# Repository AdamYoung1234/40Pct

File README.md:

The SmallFry 40% Board
=====

##NOTICE
* This repo is a fork of Regack's 40Pct
* This repo is under CC-BY-SA 3.0 Liscense
* PLEASE MAKE SURE YOU FULLY UNDERSTAND THIS LISCENSE BEFORE YOU USE THE DESIGN.
* 请确保在使用之前完全理解了 CC-BY-SA 3.0协议.

## To-do list
* Add the global backlight

## v0.11
* Change the cystal package to HC49
* Change the mini USB package from SMD to TH

## v0.8-v0.10
* I forget everything that I did, lots of little things
* fixed some unconnected pads (oops)
* cleaned up silkscreens again
* fixed diode pads to fit SOD-123 footprint
* fixed BOM info for components
* rounded PCB edges
* replaced slotted holes with... holes
* added Vcc and Gnd pins to LED expansion
* changed LED expansion pins to 2.54 pitch

## v0.7 - 2013.10.20
* cleaned up silkscreens
* moved 'ROW5' expansion to GPIO7 (still ATMEGA32U4 pin8/PB0)
* added notes
* cleaned up and removed extra libs/mods

## v0.6 - 2013.10.16
* pulled extra pin for ROW5 from ATMEGA pin 8/PB0
* changed drills for holes/slots to work with OSHpark 
* added GPIO4, GPIO5, GPIO6 connectors to ATMEGA pins 26/PD6, 22/PD5, 11/PB3
* ran row and GPIO to 1.27mm headers on right-side of board for interconnect (ribbon cable spacing)

## v0.5 - 2013.09.20
* added back missing slot on right side of board
* added LEDs for optional keys from v0.4
* generated pcb image * not sure why slots don't render properly
* removed bottom-of-board expansion pins

## v0.4 - 2013.09.19
* added optional 1.25+1.0 and 1.0+1.25 for right-shift/fn keys

## v0.3 - 2013.09.18
* based on the GH60 Rev B PCB
* SMT ATMEGA32U4 and other components on back of board
* Expansion ports on bottom and top row
* LEDs on ESC, 'CAPS', and WASD Cluster
* Other LEDs in matrix with expansion points on top row

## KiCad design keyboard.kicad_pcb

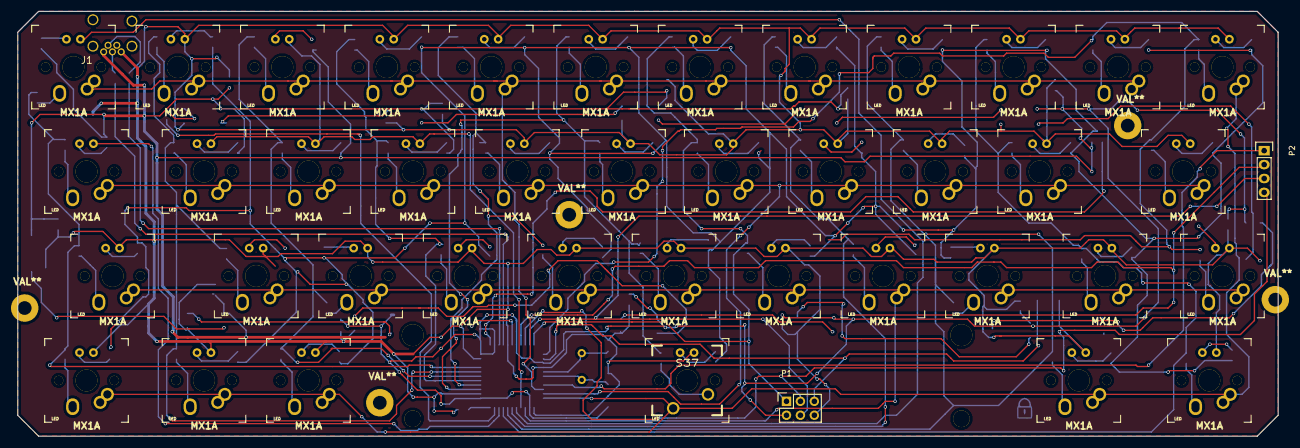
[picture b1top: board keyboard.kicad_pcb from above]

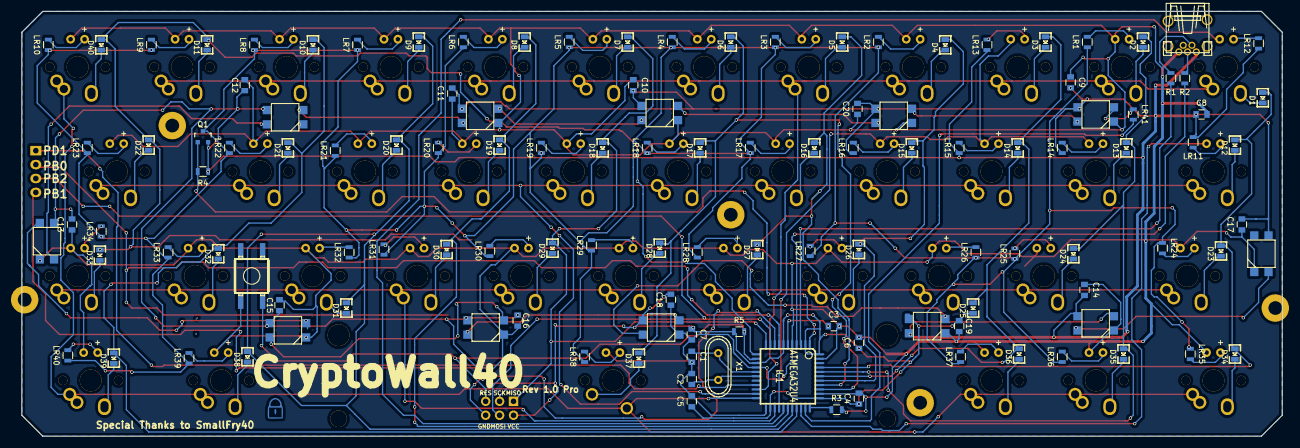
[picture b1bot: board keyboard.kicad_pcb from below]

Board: 2 copper layers, 229.9 x 77.5 mm, 210 parts (123 on the bottom side), 128 nets.

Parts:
C1, C2: 22pF; C_0805
C3, C8: 1uF; C_0805
C4, C5, C6, C7, C9, C10, C11, C12, C13, C14, C15, C16, C17, C18, C19, C20: 100nF; C_0805
D1, D2, D3, D4, D5, D6, D7, D8, D9, D10, D11, D12, D13, D14, D15, D16, D17, D18, D19, D20, D21, D22, D23, D24, D25, D26, D27, D28, D29, D30, D31, D32, D33, D34, D35, D36, D37, D38, D39, D40: DIODE; SM0805D
IC1: ATMEGA32U4; TQFP44
J1: USBMINI_B05; DX_USB
LED1, LED2, LED3, LED4, LED5, LED6, LED7, LED8, LED9, LED10, LED11, LED12, LED13, LED14, LED15, LED16, LED17, LED18, LED19, LED20, LED21, LED22, LED23, LED24, LED25, LED26, LED27, LED28, LED29, LED30, LED31, LED32, LED33, LED34, LED35, LED36, LED37, LED38, LED39, LED40: LED; MX1A-led
LR1, LR2, LR3, LR4, LR5, LR6, LR7, LR8, LR9, LR10, LR11, LR12, LR13, LR14, LR15, LR16, LR17, LR18, LR19, LR20, LR21, LR22, LR23, LR24, LR25, LR26, LR27, LR28, LR29, LR30, LR31, LR32, LR33, LR34, LR35, LR36, LR37, LR38, LR39, LR40, LR41: 330R; R_0805
MXLED: VAL**; PKRHC
MXLED#2, MXLED#3, MXLED#4, MXLED#5: VAL**; PKRHC
P1: ISP; Socket_Strip_Straight_2x03
P2: GPIO Port; Socket_Strip_Straight_1x04
Q1: MOS_P; SOT-23
R1, R2: 22R; R_0805
R3, R4, R5: 10K; R_0805
RGBLED1, RGBLED2, RGBLED3, RGBLED4, RGBLED5, RGBLED6, RGBLED7, RGBLED8, RGBLED9, RGBLED10, RGBLED11, RGBLED12: WS2812B
S0: DTSM-6
S1, S2, S3, S4, S5, S6, S7, S8, S9, S10, S11, S12, S13, S14, S15, S16, S17, S18, S19, S20, S21, S22, S23, S24, S25, S26, S27, S28, S29, S30, S31, S32, S33, S34, S35, S36, S38, S39, S40: MX1A; MX1ALPS
S37: MX1A; CHERRY_PCB_625H_Rev
X1: CRYSTAL; Crystal_HC49-U_Vertical

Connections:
/GPIO0: IC1.10, P1.4, P2.3
/GPIO1: IC1.9, P1.3, P2.4
/GPIO2: IC1.8, P2.2
/GPIO3: IC1.19, P2.1
/Matrix/Col0: D1.1, D12.1, D23.1, D34.1, IC1.41
/Matrix/Col1: D2.1, D13.1, D24.1, D35.1, IC1.40
/Matrix/Col2: D3.1, D14.1, D25.1, D36.1, IC1.39
/Matrix/Col3: D4.1, D15.1, D26.1, IC1.38
/Matrix/Col4: D5.1, D16.1, D27.1, IC1.37
/Matrix/Col5: D6.1, D17.1, D28.1, D37.1, IC1.36
/Matrix/Col6: D7.1, D18.1, D29.1, IC1.11, P1.1
/Matrix/Col7: D8.1, D19.1, D30.1, IC1.28
/Matrix/Col8: D9.1, D20.1, D31.1, D38.1, IC1.29
/Matrix/Col9: D10.1, D21.1, D32.1, D39.1, IC1.30
/Matrix/Col10: D11.1, D22.1, D33.1, D40.1, IC1.12
/Matrix/Row0: IC1.20, S1.1, S2.1, S3.1, S4.1, S5.1, S6.1, S7.1, S8.1, S9.1, S10.1, S11.1
/Matrix/Row1: IC1.21, S12.1, S13.1, S14.1, S15.1, S16.1, S17.1, S18.1, S19.1, S20.1, S21.1, S22.1
/Matrix/Row2: IC1.25, S23.1, S24.1, S25.1, S26.1, S27.1, S28.1, S29.1, S30.1, S31.1, S32.1, S33.1
/Matrix/Row3: IC1.22, S34.1, S35.1, S36.1, S37.1, S38.1, S39.1, S40.1
/led/Backlight: IC1.1, Q1.G, R4.2
/led/Bottom: IC1.32, LR41.2
/led/CapsLock: IC1.31, LED11.2
/led/ESC: IC1.27, LED12.2
/led/LRow0: LR1.1, LR2.1, LR3.1, LR4.1, LR5.1, LR6.1, LR7.1, LR8.1, LR9.1, LR10.1, LR17.1, LR18.1, LR19.1, LR20.1, LR21.1, LR22.1, LR23.1, LR24.1, LR25.1, LR26.1, LR27.1, LR28.1, LR29.1, LR30.1, LR31.1, LR32.1, LR33.1, LR34.1, LR35.1, LR36.1, LR37.1, LR38.1, LR39.1, LR40.1, Q1.D
/led/WASD: IC1.26, LED13.2, LED14.2, LED15.2, LED16.2
/~Res: IC1.13, P1.5, R5.2, S0.3
GND: C1.2, C2.2, C3.2, C4.2, C5.2, C6.2, C7.2, C8.2, C9.1, C10.1, C11.1, C12.1, C13.1, C14.1, C15.1, C16.1, C17.1, C18.1, C19.1, C20.1, IC1.5, IC1.15, IC1.23, IC1.35, IC1.43, J1.5, LED1.2, LED2.2, LED3.2, LED4.2, LED5.2, LED6.2, LED7.2, LED8.2, LED9.2, LED10.2, LED17.2, LED18.2, LED19.2, LED20.2, LED21.2, LED22.2, LED23.2, LED24.2, LED25.2, LED26.2, LED27.2, LED28.2, LED29.2, LED30.2, LED31.2, LED32.2, LED33.2, LED34.2, LED35.2, LED36.2, LED37.2, LED38.2, LED39.2, LED40.2, P1.6, R3.2, RGBLED1.3, RGBLED2.3, RGBLED3.3, RGBLED4.3, RGBLED5.3, RGBLED6.3, RGBLED7.3, RGBLED8.3, RGBLED9.3, RGBLED10.3, RGBLED11.3, RGBLED12.3, S0.1
unnamed: C1.1, IC1.16, X1.1
unnamed: C2.1, IC1.17, X1.2
unnamed: C3.1, IC1.6
unnamed: D1.2, S1.2
unnamed: D2.2, S2.2
unnamed: D3.2, S3.2
unnamed: D4.2, S4.2
unnamed: D5.2, S5.2
unnamed: D6.2, S6.2
unnamed: D7.2, S7.2
unnamed: D8.2, S8.2
unnamed: D9.2, S9.2
unnamed: D10.2, S10.2
unnamed: D11.2, S11.2
unnamed: D12.2, S12.2
unnamed: D13.2, S13.2
unnamed: D14.2, S14.2
unnamed: D15.2, S15.2
unnamed: D16.2, S16.2
unnamed: D17.2, S17.2
unnamed: D18.2, S18.2
unnamed: D19.2, S19.2
unnamed: D20.2, S20.2
unnamed: D21.2, S21.2
unnamed: D22.2, S22.2
unnamed: D23.2, S23.2
unnamed: D24.2, S24.2
unnamed: D25.2, S25.2
unnamed: D26.2, S26.2
unnamed: D27.2, S27.2
unnamed: D28.2, S28.2
unnamed: D29.2, S29.2
unnamed: D30.2, S30.2
unnamed: D31.2, S31.2
unnamed: D32.2, S32.2
unnamed: D33.2, S33.2
unnamed: D34.2, S34.2
unnamed: D35.2, S35.2
unnamed: D36.2, S36.2
unnamed: D37.2, S37.2
unnamed: D38.2, S38.2
unnamed: D39.2, S39.2
unnamed: D40.2, S40.2
unnamed: IC1.3, R1.1
unnamed: IC1.4, R2.1
unnamed: IC1.33, R3.1
unnamed: J1.2, R1.2
unnamed: J1.3, R2.2
unnamed: LED1.1, LR1.2
unnamed: LED2.1, LR2.2
unnamed: LED3.1, LR3.2
unnamed: LED4.1, LR4.2
unnamed: LED5.1, LR5.2
unnamed: LED6.1, LR6.2
unnamed: LED7.1, LR7.2
unnamed: LED8.1, LR8.2
unnamed: LED9.1, LR9.2
unnamed: LED10.1, LR10.2
unnamed: LED11.1, LR11.2
unnamed: LED12.1, LR12.2
unnamed: LED13.1, LR13.2
unnamed: LED14.1, LR14.2
unnamed: LED15.1, LR15.2
unnamed: LED16.1, LR16.2
unnamed: LED17.1, LR17.2
unnamed: LED18.1, LR18.2
unnamed: LED19.1, LR19.2
unnamed: LED20.1, LR20.2
unnamed: LED21.1, LR21.2
unnamed: LED22.1, LR22.2
unnamed: LED23.1, LR23.2
unnamed: LED24.1, LR24.2
unnamed: LED25.1, LR25.2
unnamed: LED26.1, LR26.2
unnamed: LED27.1, LR27.2
unnamed: LED28.1, LR28.2
unnamed: LED29.1, LR29.2
unnamed: LED30.1, LR30.2
unnamed: LED31.1, LR31.2
unnamed: LED32.1, LR32.2
unnamed: LED33.1, LR33.2
unnamed: LED34.1, LR34.2
unnamed: LED35.1, LR35.2
unnamed: LED36.1, LR36.2
unnamed: LED37.1, LR37.2
unnamed: LED38.1, LR38.2
unnamed: LED39.1, LR39.2
unnamed: LED40.1, LR40.2
unnamed: LR41.1, RGBLED1.4
unnamed: RGBLED1.2, RGBLED2.4
unnamed: RGBLED2.2, RGBLED3.4
unnamed: RGBLED3.2, RGBLED4.4
unnamed: RGBLED4.2, RGBLED5.4
unnamed: RGBLED5.2, RGBLED6.4
unnamed: RGBLED6.2, RGBLED7.4
unnamed: RGBLED7.2, RGBLED8.4
unnamed: RGBLED8.2, RGBLED9.4
unnamed: RGBLED10.2, RGBLED11.4
unnamed: RGBLED9.2, RGBLED10.4
unnamed: RGBLED11.2, RGBLED12.4
VCC: C4.1, C5.1, C6.1, C7.1, C8.1, C9.2, C10.2, C11.2, C12.2, C13.2, C14.2, C15.2, C16.2, C17.2, C18.2, C19.2, C20.2, IC1.2, IC1.7, IC1.14, IC1.24, IC1.34, IC1.44, J1.1, LR11.1, LR12.1, LR13.1, LR14.1, LR15.1, LR16.1, P1.2, Q1.S, R4.1, R5.1, RGBLED1.1, RGBLED2.1, RGBLED3.1, RGBLED4.1, RGBLED5.1, RGBLED6.1, RGBLED7.1, RGBLED8.1, RGBLED9.1, RGBLED10.1, RGBLED11.1, RGBLED12.1

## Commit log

2016-05-14 Change the cyrstal footprint / correct two wrong diode directions
2016-05-15 Change the footprint of MiniUSB
2016-05-15 Add the latest gerber and change the readme file
2016-05-21 Rebuild the project using latest kicad
    Rebuild the project using latest kicad, leaving eschematic and pcb
    unfinished
2016-05-21 Add the README file
2016-05-21 Final touches on schematic
2016-06-02 Minor Changes
2016-06-17 ver 0.12
2016-06-18 Fix a mistake in underglow
2016-06-18 Update Gerber files
2016-06-23 Slight changes on edge
    Gerber files updated also.
2016-07-01 a lot of changes
2016-07-02 minor changes & update gerber files
2016-07-02 Add BOM
2016-07-03 add gerber.rar
2016-07-09 final version
2016-07-10 update bom
2016-07-11 Update Silkscreen
2016-07-13 Rev 1.0 Pro
